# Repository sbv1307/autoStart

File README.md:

# AutoStart module.

A peace of hardware, which controls an open collector output, based on energy mesured by a AC Current Sensor Transformer (CT).

This project is about securing a waterpump.

The idea is to monitor if the waterpump is running too long, and then break the power if that's the case.

Power is controlled by IHC®. To monitor if the waterpump is running, this autoStart moduld is used.
The CT will mesure if the waterpump is running or not, at the open collector output will be connected to a IHC® Input 24/x module.
A FunctionBlock in the IHC® Controller will then take action, when the Input on the IHC® Input 24/x module is held active too long, 
and schwitch OFF the power for the water pumnp.

Alternativle the AutoStart module can be used to controll a Vaccum cleaner. E.g. turn the Vaccum cleaner ON while a electric hand tool is used.

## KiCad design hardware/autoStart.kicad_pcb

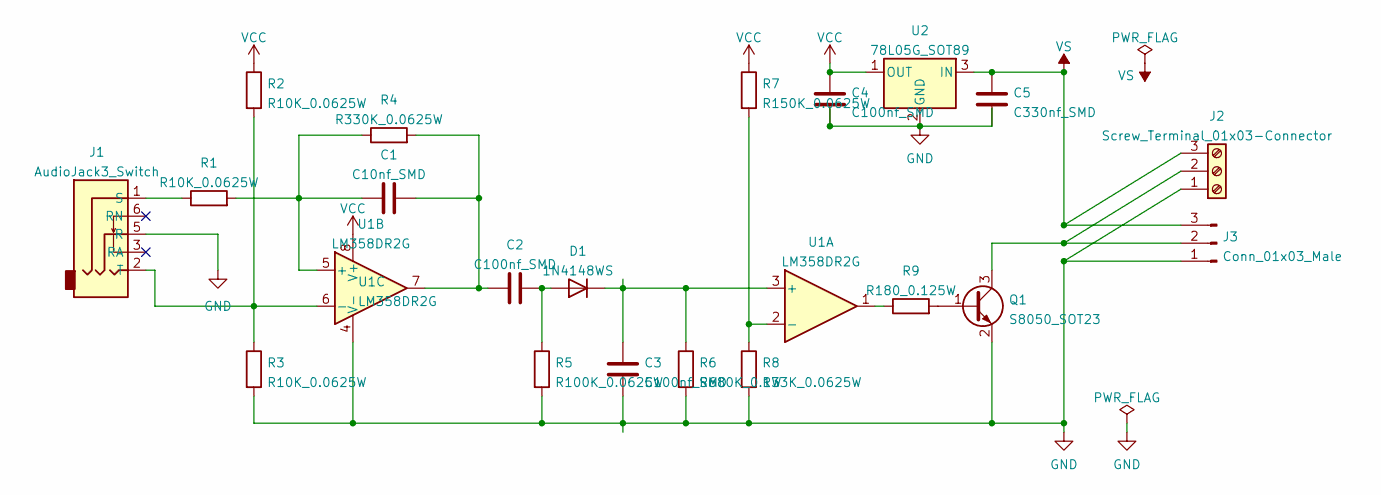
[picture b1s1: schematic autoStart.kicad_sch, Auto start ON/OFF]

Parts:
C1: C10nf_SMD; C_0402_1005Metric; MFR.Part # CL05B103KB5NNNC; JLCPCB Part # C15195
C2, C3, C4: C100nf_SMD; C_0402_1005Metric; MFR.Part # CL05B104KO5NNNC; JLCPCB Part # C1525
C5: C330nf_SMD; C_0805_2012Metric; MFR.Part # 0805B334K500NT; JLCPCB Part # C1740
D1: 1N4148WS; D_SOD-323F; MFR.Part # 1N4148WS; JLCPCB Part # C2128
J1: AudioJack3_Switch; AUDIO_JACK_ASJ-195-L-HT-(Backside_Mount)
J2: Screw_Terminal_01x03-Connector; Phoenix_TERM_BLOCK_3POS_45DEG_5MM_PCB; Manufacturer Part # 1988817; Digi-Key Part # 277-1765-ND
J3: Conn_01x03_Male; PinHeader_1x03_P_5mm_Vertical-(Backside_Mount)
Q1: S8050_SOT23; SOT-23; Manufacturer PN SS8050; JLCPCB Part # C2150
R1, R2, R3: R10K_0.0625W; R_0402_1005Metric; Manufacturer PN 0402WGF1002TCE; JLCPCB Part # C25744
R4: R330K_0.0625W; R_0402_1005Metric; Manufacturer PN 0402WGF3303TCE; JLCPCB Part # C25778
R5: R100K_0.0625W; R_0402_1005Metric; Manufacturer PN 0402WGF1003TCE; JLCPCB Part # C25741
R6: R680K_0.1W; R_0201_0603Metric; Manufacturer PN 0603WAF6803T5E; JLCPCB Part # C25822
R7: R150K_0.0625W; R_0402_1005Metric; Manufacturer PN 0402WGF1503TCE; JLCPCB Part # C25755
R8: R33K_0.0625W; R_0402_1005Metric; Manufacturer PN 0402WGF3302TCE; JLCPCB Part # C25779
R9: R180_0.125W; R_0805_2012Metric; Manufacturer PN 0805W8F1800T5E; JLCPCB Part # C25270
U1: LM358DR2G; SOIC-8_3.9x4.9mm_P1.27mm; MFR.Part # LM358DR2G; JLCPCB Part # C7950
U2: 78L05G_SOT89; SOT-89-3; MFR.Part # 78L05G-AB3-R; JLCPCB Part # C71136

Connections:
GND: C3.2, C4.2, C5.2, J1.5 (R), J2.1, J3.1, Q1.2 (E), R3.2, R5.2, R6.2, R8.2, U1.4 (V-), U2.2 (GND)
unnamed: C1.1, R1.2, R4.1, U1.5 (+)
unnamed: C1.2, C2.1, R4.2, U1.7
unnamed: C2.2, D1.2 (A), R5.1
unnamed: C3.1, D1.1 (K), R6.1, U1.3 (+)
unnamed: J1.1 (S), R1.1
unnamed: J1.2 (T), R2.2, R3.1, U1.6 (-)
unnamed: J2.2, J3.2, Q1.3 (C)
unnamed: Q1.1 (B), R9.2
unnamed: R7.2, R8.1, U1.2 (-)
unnamed: R9.1, U1.1
VCC: C4.1, R2.1, R7.1, U1.8 (V+), U2.1 (OUT)
VS: C5.1, J2.3, J3.3, U2.3 (IN)

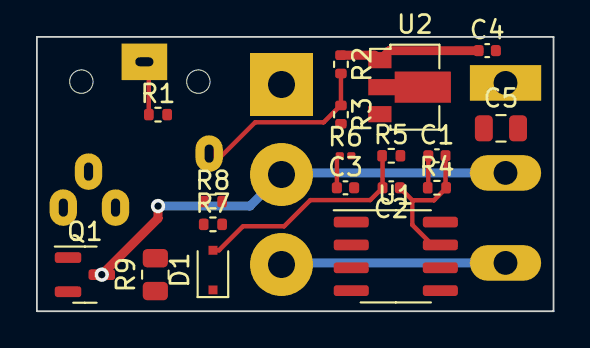
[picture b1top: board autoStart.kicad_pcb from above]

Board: 2 copper layers, 28.7 x 15.2 mm, 21 parts (0 on the bottom side), 13 nets.

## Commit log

2022-03-01 schematics update
2022-03-09 Project prepared for converting to SMD
2022-03-09 Doc.: README.md updated
2022-03-20 Final THT Mount commit
2022-03-25 SMD Mounts Initial commit
